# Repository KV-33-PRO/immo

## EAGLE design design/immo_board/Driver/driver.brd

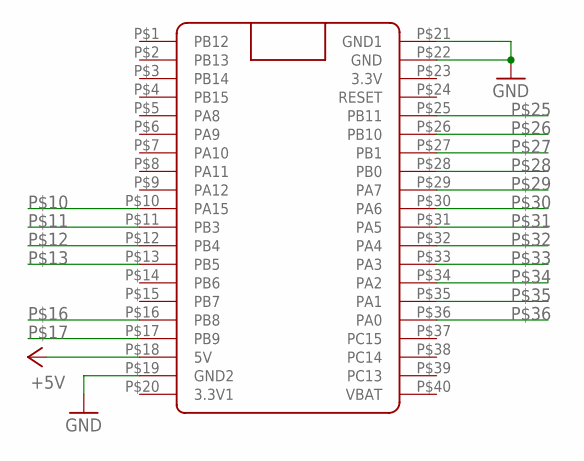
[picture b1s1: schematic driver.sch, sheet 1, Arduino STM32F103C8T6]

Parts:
U$1: STM32F103C8T6; BLUE_PILL_ADV

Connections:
+5V: U$1.P$18 (5V); also elsewhere on the board
GND: U$1.P$19 (GND2), U$1.P$21 (GND1), U$1.P$22 (GND); also elsewhere on the board
P$10: U$1.P$10 (PA15); also elsewhere on the board
P$11: U$1.P$11 (PB3); also elsewhere on the board
P$12: U$1.P$12 (PB4); also elsewhere on the board
P$13: U$1.P$13 (PB5); also elsewhere on the board
P$16: U$1.P$16 (PB8); also elsewhere on the board
P$17: U$1.P$17 (PB9); also elsewhere on the board
P$25: U$1.P$25 (PB11); also elsewhere on the board
P$26: U$1.P$26 (PB10); also elsewhere on the board
P$27: U$1.P$27 (PB1); also elsewhere on the board
P$28: U$1.P$28 (PB0); also elsewhere on the board
P$29: U$1.P$29 (PA7); also elsewhere on the board
P$30: U$1.P$30 (PA6); also elsewhere on the board
P$31: U$1.P$31 (PA5); also elsewhere on the board
P$32: U$1.P$32 (PA4); also elsewhere on the board
P$33: U$1.P$33 (PA3); also elsewhere on the board
P$34: U$1.P$34 (PA2); also elsewhere on the board
P$35: U$1.P$35 (PA1); also elsewhere on the board
P$36: U$1.P$36 (PA0); also elsewhere on the board

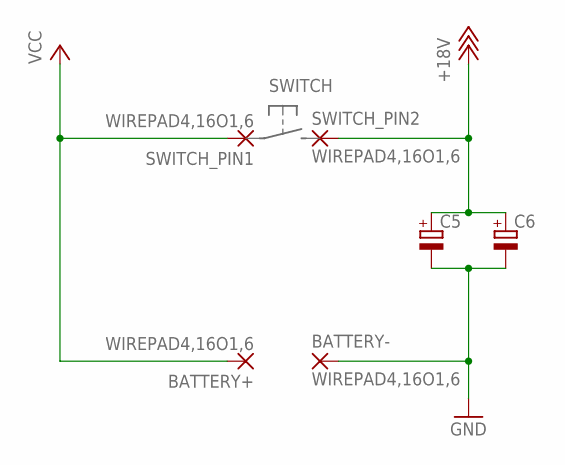
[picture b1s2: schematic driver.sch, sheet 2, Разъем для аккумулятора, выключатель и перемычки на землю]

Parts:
BATTERY+: WIREPAD4,16O1,6; 4,16O1,6
BATTERY-: WIREPAD4,16O1,6; 4,16O1,6
C5: CPOL-EUE5-8.5; E5-8,5
C6: CPOL-EUE2.5-5; E2,5-5
SWITCH_PIN1, SWITCH_PIN2: WIREPAD4,16O1,6; 4,16O1,6

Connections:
+18V: C5.+, C6.+, SWITCH_PIN2.1; also elsewhere on the board
GND: BATTERY-.1, C5.-, C6.-; also elsewhere on the board
VCC: BATTERY+.1, SWITCH_PIN1.1

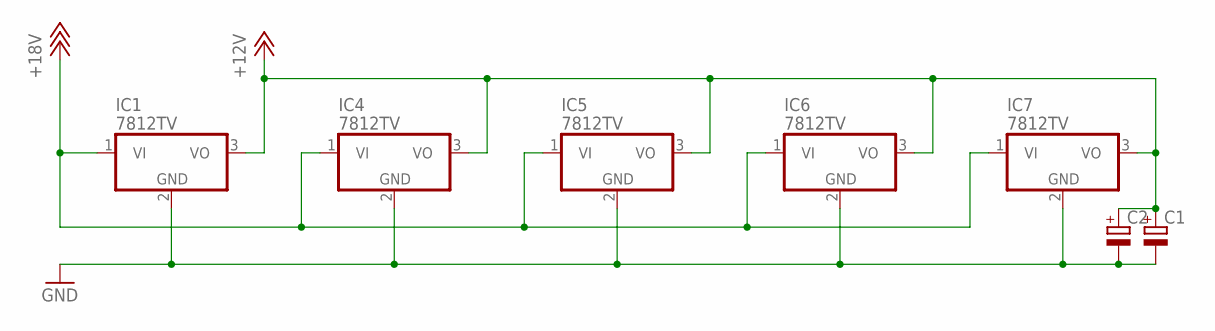
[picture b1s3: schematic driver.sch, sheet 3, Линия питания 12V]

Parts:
C1: CPOL-EUE5-8.5; E5-8,5
C2: CPOL-EUE2.5-5; E2,5-5
IC1, IC4, IC5, IC6, IC7: 7812TV; TO220V

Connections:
+12V: C1.+, C2.+, IC1.3 (VO), IC4.3 (VO), IC5.3 (VO), IC6.3 (VO), IC7.3 (VO); also elsewhere on the board
+18V: IC1.1 (VI), IC4.1 (VI), IC5.1 (VI), IC6.1 (VI), IC7.1 (VI); also elsewhere on the board
GND: C1.-, C2.-, IC1.2 (GND), IC4.2 (GND), IC5.2 (GND), IC6.2 (GND), IC7.2 (GND); also elsewhere on the board

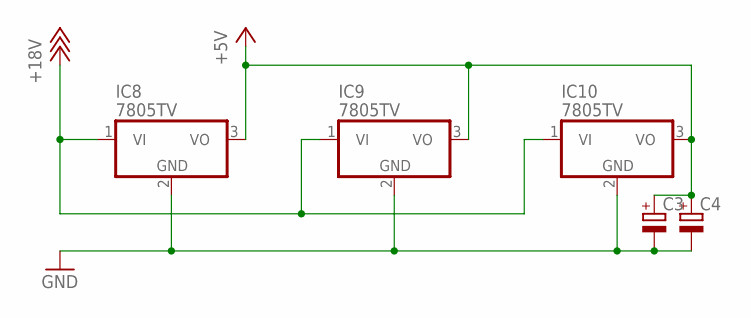
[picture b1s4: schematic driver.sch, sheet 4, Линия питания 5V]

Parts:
C3: CPOL-EUE2.5-5; E2,5-5
C4: CPOL-EUE5-8.5; E5-8,5
IC8, IC9, IC10: 7805TV; TO220V

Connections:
+5V: C3.+, C4.+, IC8.3 (VO), IC9.3 (VO), IC10.3 (VO); also elsewhere on the board
+18V: IC8.1 (VI), IC9.1 (VI), IC10.1 (VI); also elsewhere on the board
GND: C3.-, C4.-, IC8.2 (GND), IC9.2 (GND), IC10.2 (GND); also elsewhere on the board

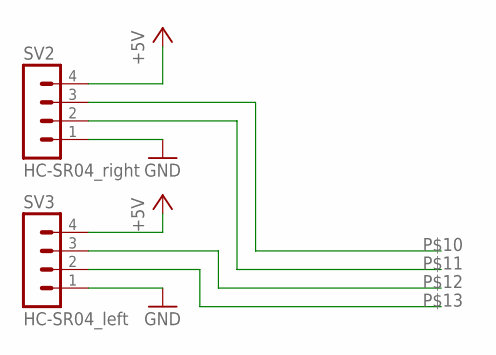
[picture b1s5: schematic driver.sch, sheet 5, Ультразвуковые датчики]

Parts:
SV2: HC-SR04_right; MA04-1
SV3: HC-SR04_left; MA04-1

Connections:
+5V: SV2.4, SV3.4; also elsewhere on the board
GND: SV2.1, SV3.1; also elsewhere on the board
P$10: SV2.3; also elsewhere on the board
P$11: SV2.2; also elsewhere on the board
P$12: SV3.3; also elsewhere on the board
P$13: SV3.2; also elsewhere on the board

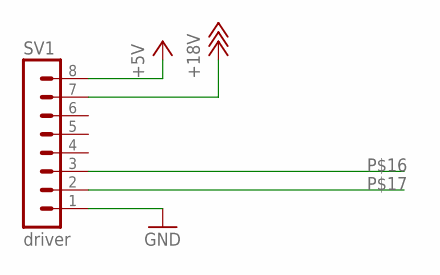
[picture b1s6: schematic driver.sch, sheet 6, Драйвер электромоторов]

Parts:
SV1: driver; MA08-1

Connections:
+5V: SV1.8; also elsewhere on the board
+18V: SV1.7; also elsewhere on the board
GND: SV1.1; also elsewhere on the board
P$16: SV1.3; also elsewhere on the board
P$17: SV1.2; also elsewhere on the board

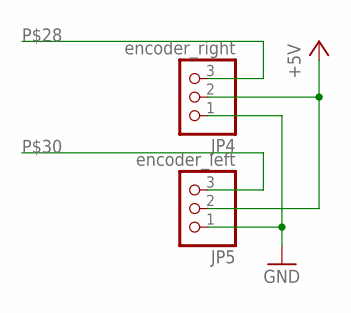
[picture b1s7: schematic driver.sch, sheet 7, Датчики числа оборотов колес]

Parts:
JP4: encoder_right; 1X03
JP5: encoder_left; 1X03

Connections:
+5V: JP4.2, JP5.2; also elsewhere on the board
GND: JP4.1, JP5.1; also elsewhere on the board
P$28: JP4.3; also elsewhere on the board
P$30: JP5.3; also elsewhere on the board

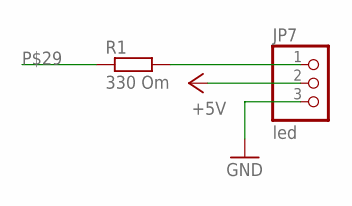
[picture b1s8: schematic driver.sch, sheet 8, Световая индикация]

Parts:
JP7: led; 1X03
R1: 330 Om; 0207/12

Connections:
+5V: JP7.2; also elsewhere on the board
GND: JP7.3; also elsewhere on the board
unnamed: JP7.1, R1.2
P$29: R1.1; also elsewhere on the board

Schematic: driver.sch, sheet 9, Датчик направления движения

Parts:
IC2: LM393N; DIL08
JP2: motor_direction; 1X02
R12, R13: 10 kOm; 0207/12

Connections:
+5V: IC2.8 (V+), R12.1, R13.2; also elsewhere on the board
GND: IC2.3 (+IN), IC2.4 (V-), IC2.5 (+IN); also elsewhere on the board
unnamed: IC2.2 (-IN), JP2.1
unnamed: IC2.6 (-IN), JP2.2
P$31: IC2.7 (OUT), R13.1; also elsewhere on the board
P$32: IC2.1 (OUT), R12.2; also elsewhere on the board

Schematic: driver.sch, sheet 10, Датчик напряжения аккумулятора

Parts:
JP6: battery_balance; 1_05X2MM
R2, R3, R4, R5: 3,3 kOm; 0207/15
R6, R7, R8, R9: 330 Om; 0207/15

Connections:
GND: JP6.5, R6.1, R7.1, R8.1, R9.1; also elsewhere on the board
unnamed: JP6.4, R5.2
unnamed: JP6.2, R4.2
unnamed: JP6.3, R3.2
unnamed: JP6.1, R2.2
P$33: R2.1, R6.2; also elsewhere on the board
P$34: R3.1, R7.2; also elsewhere on the board
P$35: R4.1, R8.2; also elsewhere on the board
P$36: R5.1, R9.2; also elsewhere on the board

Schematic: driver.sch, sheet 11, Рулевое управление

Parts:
IC3: 74LS241N; DIL20
JP1: dynamixel; 1X03

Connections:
+5V: IC3.20 (VCC); also elsewhere on the board
+12V: JP1.2; also elsewhere on the board
GND: IC3.10 (GND), JP1.1; also elsewhere on the board
unnamed: IC3.2 (A1), IC3.3 (Y4), JP1.3
P$25: IC3.18 (Y1); also elsewhere on the board
P$26: IC3.17 (A4); also elsewhere on the board
P$27: IC3.1 (G), IC3.19 (G); also elsewhere on the board

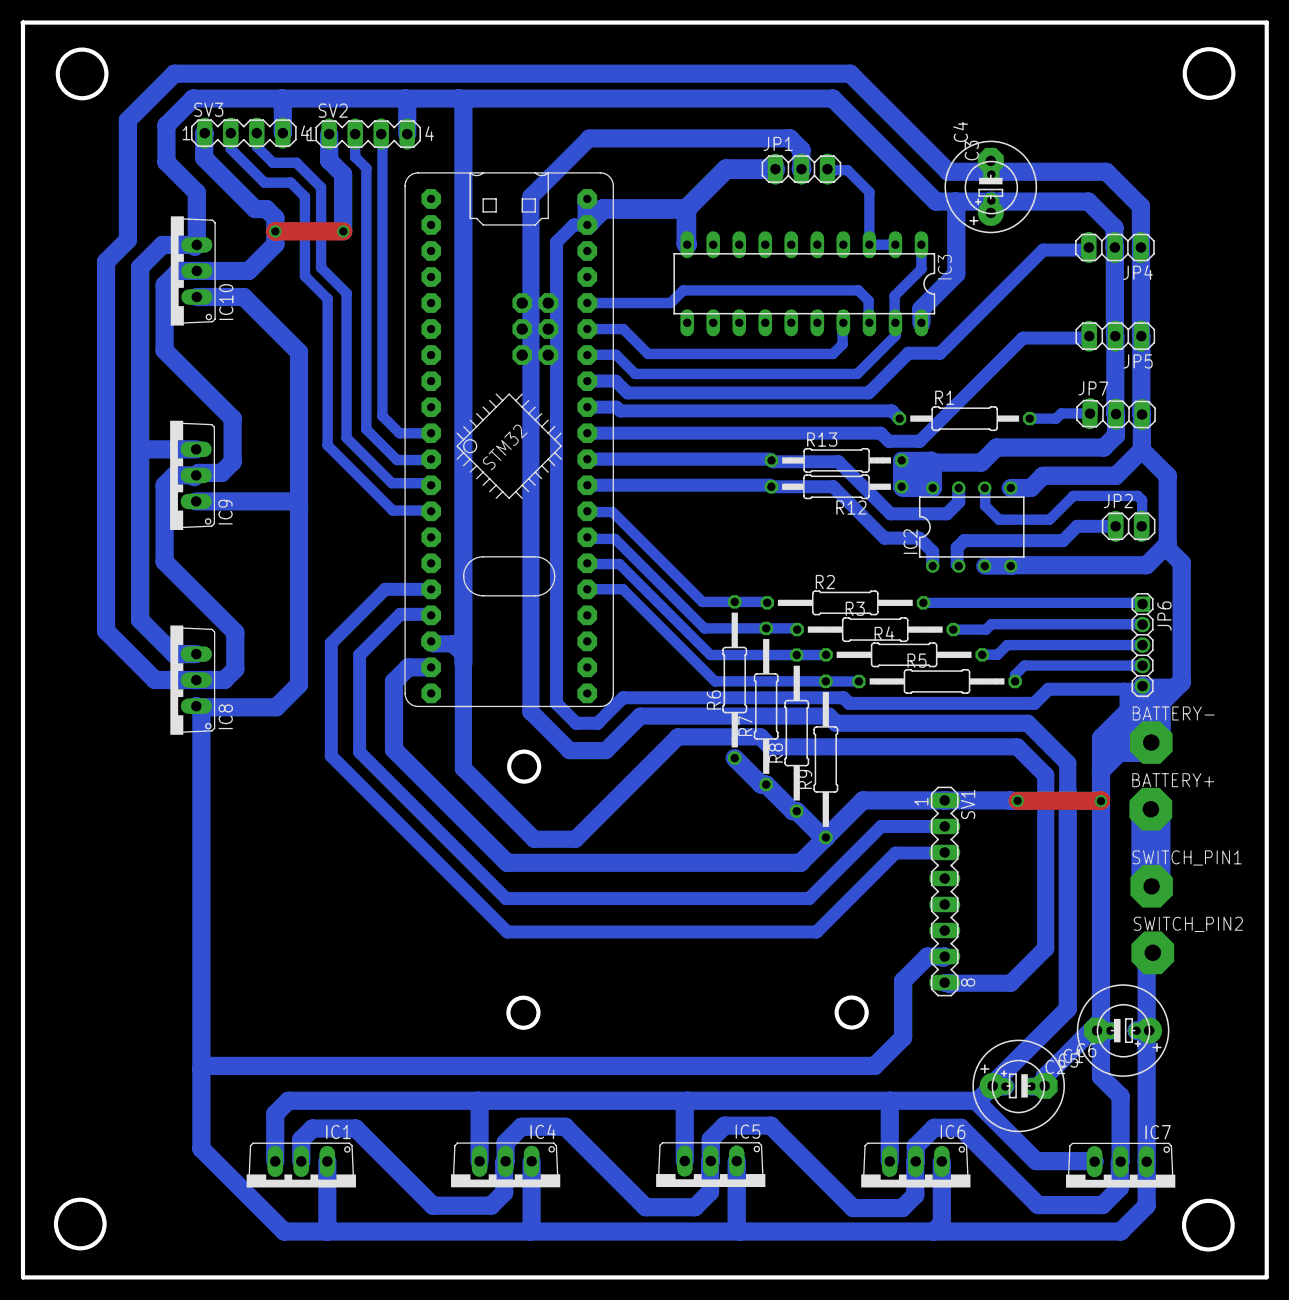
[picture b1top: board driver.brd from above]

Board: 2 copper layers, 121.4 x 122.5 mm, 41 parts (0 on the bottom side), 31 nets.

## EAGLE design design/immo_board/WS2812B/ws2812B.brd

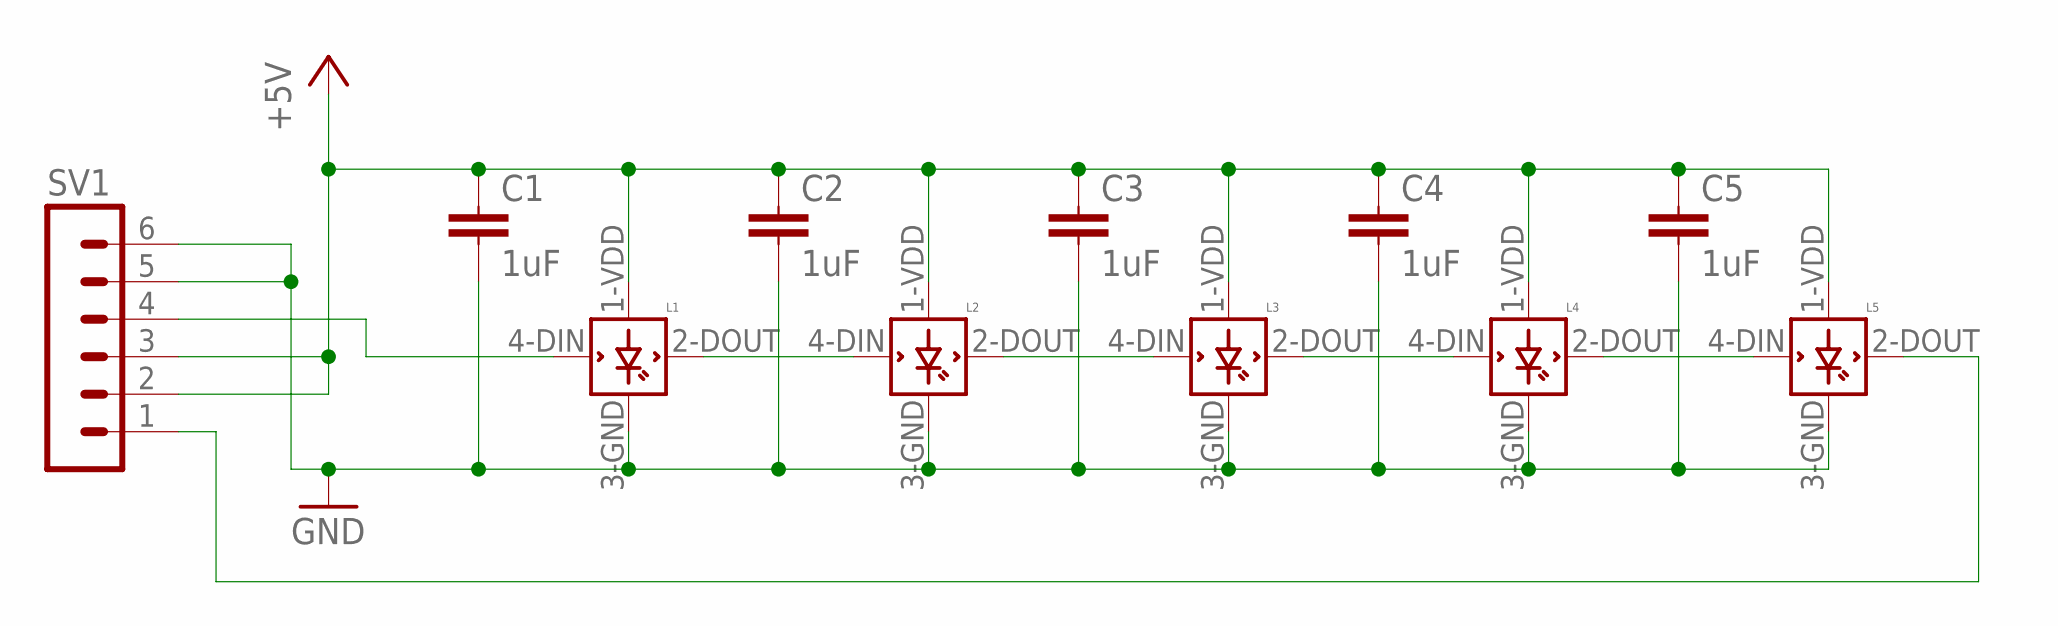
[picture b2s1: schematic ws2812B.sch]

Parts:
C1, C2, C3, C4, C5: 1uF; C10B4
L1, L2, L3, L4, L5: WS2812B
SV1: MA06-1

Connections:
+5V: C1.1, C2.1, C3.1, C4.1, C5.1, L1.1-VDD (VDD), L2.1-VDD (VDD), L3.1-VDD (VDD), L4.1-VDD (VDD), L5.1-VDD (VDD), SV1.2, SV1.3
GND: C1.2, C2.2, C3.2, C4.2, C5.2, L1.3-GND (GND), L2.3-GND (GND), L3.3-GND (GND), L4.3-GND (GND), L5.3-GND (GND), SV1.5, SV1.6
unnamed: L1.4-DIN (DIN), SV1.4
unnamed: L4.2-DOUT (DOUT), L5.4-DIN (DIN)
unnamed: L5.2-DOUT (DOUT), SV1.1
unnamed: L1.2-DOUT (DOUT), L2.4-DIN (DIN)
unnamed: L2.2-DOUT (DOUT), L3.4-DIN (DIN)
unnamed: L3.2-DOUT (DOUT), L4.4-DIN (DIN)

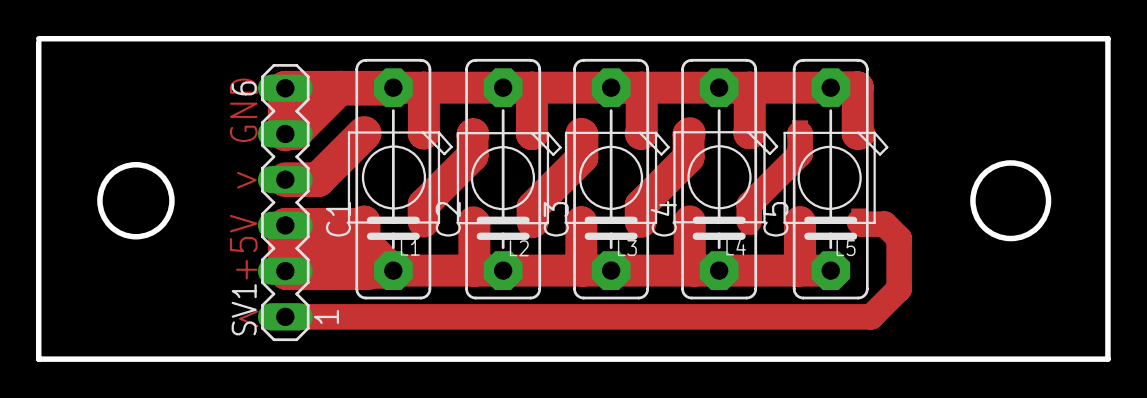
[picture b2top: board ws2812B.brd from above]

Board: 2 copper layers, 59.4 x 17.8 mm, 11 parts (0 on the bottom side), 8 nets.

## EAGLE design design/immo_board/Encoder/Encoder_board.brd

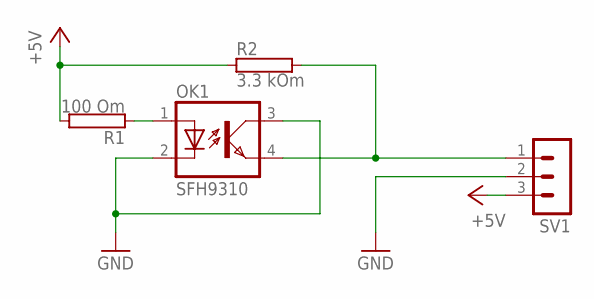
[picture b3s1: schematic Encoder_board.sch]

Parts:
OK1: SFH9310
R1: 100 Om; RS1/4
R2: 3.3 kOm; RS1/4
SV1: MA03-1

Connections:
+5V: R1.2, R2.1, SV1.3
GND: OK1.2 (C), OK1.3 (COL), SV1.2
unnamed: OK1.1 (A), R1.1
SIG: OK1.4 (EMIT), R2.2, SV1.1

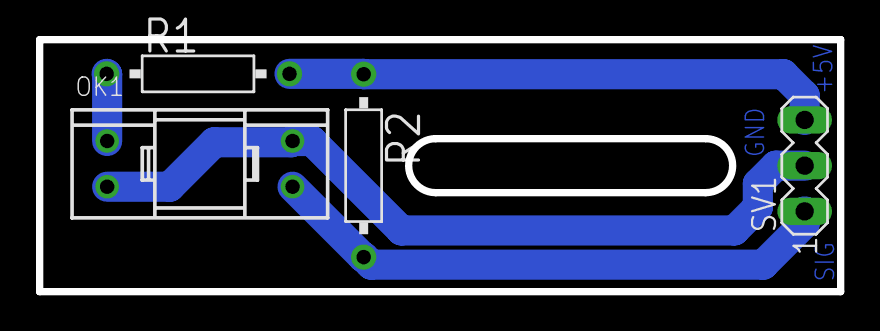
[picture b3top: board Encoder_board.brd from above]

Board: 2 copper layers, 44.5 x 14.0 mm, 4 parts (0 on the bottom side), 4 nets.

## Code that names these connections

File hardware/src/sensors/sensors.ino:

#include <ros.h>
#include <sensor_msgs/Range.h>
#include <Ultrasonic.h>
#include <SimpleKalmanFilter.h>

#define RATE_MS       20

ros::NodeHandle nh;

sensor_msgs::Range snr_l_msg;
sensor_msgs::Range snr_r_msg;

ros::Publisher snr_l_pub("range/front/left_snr", &snr_l_msg);
ros::Publisher snr_r_pub("range/front/right_snr", &snr_r_msg);

unsigned long last_ms;
Ultrasonic sonar_l(PA15, PB3);
Ultrasonic sonar_r(PB4, PB5);

SimpleKalmanFilter kf_l(2, 2, 0.01);
SimpleKalmanFilter kf_r(2, 2, 0.01);

void setup()
{
  nh.getHardware()->setBaud(500000);
  nh.initNode();
  nh.advertise(snr_l_pub);
  nh.advertise(snr_r_pub);

  snr_l_msg.header.frame_id =  "/left_snr";
  snr_l_msg.field_of_view = 0.10000000149;
  snr_l_msg.min_range = 0.3;
  snr_l_msg.max_range = 3.5;

  snr_r_msg.header.frame_id =  "/right_snr";
  snr_r_msg.field_of_view = 0.10000000149;
  snr_r_msg.min_range = 0.3;
  snr_r_msg.max_range = 3.5;
}

void loop()
{
  if ((millis() - last_ms) > RATE_MS) {
    last_ms = millis();

    snr_l_msg.range = kf_l.updateEstimate(sonar_l.read()/100.0);
    snr_l_msg.header.stamp = nh.now();
    snr_l_pub.publish(&snr_l_msg);

    snr_r_msg.range = kf_r.updateEstimate(sonar_r.read()/100.0);
    snr_r_msg.header.stamp = nh.now();
    snr_r_pub.publish(&snr_r_msg);

  }
  nh.spinOnce();
}

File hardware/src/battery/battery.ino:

#include <ros.h>
#include <sensor_msgs/BatteryState.h>

#define RATE_MS                   20       // задержка для публикации в топик

#define BAT_BALANCE_PIN_1         PA0      // вход для балансового порта батареи 1
#define BAT_BALANCE_PIN_2         PA1      // вход для балансового порта батареи 2
#define BAT_BALANCE_PIN_3         PA2      // вход для балансового порта батареи 3
#define BAT_BALANCE_PIN_4         PA3      // вход для балансового порта батареи 4

#define BAT_VOLTAGE_MAX           16.4             // максимальный вольтаж батареи (для расчета процентов)
#define BAT_VOLTAGE_MIN           14.0             // минимальный вольтаж батареи (для расчета процентов)
#define CELL_BAT                  4                // количество банок аккумулятора

float cell_voltage[CELL_BAT] = {0, 0, 0, 0};       //секции аккумулятора
unsigned long last_ms;

ros::NodeHandle nh;
sensor_msgs::BatteryState battery_msg;

ros::Publisher battery_pub("battery", &battery_msg);                    // инициализация издателя топика "battery"

void setup() {
  pinMode(BAT_BALANCE_PIN_1, INPUT_ANALOG);
  pinMode(BAT_BALANCE_PIN_2, INPUT_ANALOG);
  pinMode(BAT_BALANCE_PIN_3, INPUT_ANALOG);
  pinMode(BAT_BALANCE_PIN_4, INPUT_ANALOG);

  nh.getHardware()->setBaud(500000);
  nh.initNode();
  nh.advertise(battery_pub);

  battery_msg.header.frame_id =  "/battery";  //заголовок
  battery_msg.cell_voltage_length = CELL_BAT; //колличество банок (элементов массива)
  battery_msg.cell_voltage = cell_voltage;    //массив значений напряжений на банках аккумулятора
  battery_msg.present = true;                 //батарея присутствует
  battery_msg.power_supply_technology = 3;    //тип батареи LiPo
  battery_msg.power_supply_status = 2;        //разряжается
  battery_msg.power_supply_health = 0;        //неизвесно
}

void loop() {
  //Читаем и записываем значения напряжений в массив
  cell_voltage[0] = analog2voltage(BAT_BALANCE_PIN_1, 0);
  cell_voltage[1] = analog2voltage(BAT_BALANCE_PIN_2, 1);
  cell_voltage[2] = analog2voltage(BAT_BALANCE_PIN_3, 2);
  cell_voltage[3] = analog2voltage(BAT_BALANCE_PIN_4, 3);

  if (millis() - last_ms >= RATE_MS) {     //публикуем не чаще чем RATE_MS
    last_ms = millis();   //фиксируем последнее время публикации сообщения в топик

    // вычисляем напряжение 2-4 секций аккумулятора
    for(int i=CELL_BAT-1;i>0;i--)
    {
       cell_voltage[i] -= cell_voltage[i-1];
    }

    battery_msg.voltage = cell_voltage[0] + cell_voltage[1] + cell_voltage[2] + cell_voltage[3];            // расчет общего напряжения аккумулятора
    battery_msg.percentage = (battery_msg.voltage - BAT_VOLTAGE_MIN) / (BAT_VOLTAGE_MAX - BAT_VOLTAGE_MIN); // считаем количество процентов возможного ресурса батареи
    if (battery_msg.percentage < 0) {
      battery_msg.percentage = 0.0;
    }
    
    battery_msg.header.stamp = nh.now();     //фиксируем время сообщения
    battery_pub.publish(&battery_msg);       //публикуем сообщение в топик

    //обнуляем данные секций
    for(int i=0;i<CELL_BAT;i++)
    {
      cell_voltage[i] = 0.0;
    }
  }
  nh.spinOnce();
}

float analog2voltage(int bat_pin, int cell) {
  float analog = analogRead(bat_pin);                     //читаем значение и преобразем в вольты
  float count = 1.0;                                      //счетчик количества элементов для расчета среднего
  if (cell_voltage[cell] > 0.0)                           //если значение в массиве уже есть, то значит нужно выводить среднее (элементов 2)
  {
    count = 2.0;
  }
  
  if (analog > 10)                                        //устанавливаем порог напряжения (фильтр шумов на входе) 
  {
    float cell_volt = 0.0088316807*analog+0.031247058;    //линейная функция тренда для расчета вольтажа
    return (cell_voltage[cell] + cell_volt)  / count;     //замеряем и записываем, затем получим среднее
  }
  else
  {
    return 0.0;
  }
}

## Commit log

2018-12-01 Fix driver.ino. Add futs_qt_odometry.
2018-12-02 Rename "futs_qt_odometry" to "odometry". Fix odometry algorithms.
2018-12-03 Add odometry.launch. Fix odometry.
2018-12-04 Fix odometry algorithms
2018-12-05 Update sensors MCU firmware
    Sensors configuration and measuring formula are updated
2018-12-06 Update sensors MCU firmware
2018-12-06 Sensors MCU firmware
    Ultrasonic rangefinder now works
2018-12-06 (Sensors MCU)fix baud
2018-12-07 Fix driver algorithm. Add support dynamixel. Add libraries for arduino.
2018-12-13 Add design project
2018-12-13 Fix include libraries. Add ros_lib for STM32 and DynamixelSerial3.
2018-12-14 Fix driver firmware (for STM32). Add picture pinout STM32F103C8T6.
2018-12-14 Fix driver firmware. Add comments for driver firmware. Add directory misc.
2018-12-15 Add immo_board for encoders. Rename IMMO to immo_design_project.
2018-12-17 Fix algorithm odometry (direction of travel). Fix port to driver.launch.
2018-12-19 Add module for battery. Move driver, sensors to "src"
2018-12-21 Fix battery (function trend line). Add results experiment.
2018-12-21 Add PID regulator for speed control motors.
2018-12-22 Add driver_move package for tests. Add battery_module in driver hardware.
2018-12-23 Fix alghoritm driver odometry and driver_move.
2018-12-24 Fix firmware sensors (stm32). Add library Ultrasonic. Delete library NewPing.
2018-12-25 Add library SimpleKalmanFilter. Fix sensors (add kalman filter for sonars).
2018-12-26 Add board and scheme for WS2812B. Move Encoder_board.brd to immo_board/ Encoder.
2018-12-26 Add library for WS2812B leds. Add firmware led indication.
2018-12-27 Fix led firmware.
2018-12-29 Add electric scheme for driver board.
2018-12-30 Add board for driver. Fix electric scheme.
2019-01-16 Fix board for driver. Fix electric scheme.
2019-01-16 Fix driver firmware (pins). Fix led firmware.
2019-01-17 Fix driver firmware.
2019-01-17 Fix driver_move. Add param in launch.
2019-01-17 Fix launch driver (add start odometry). Fix launch odometry (respawn).
2019-01-31 Fix board and electrical scheme for Encoder, Driver, WS2812B.
2019-01-31 Fix tf in odometry_node.cpp
2019-01-31 Fix board and electric scheme. Add capacitors.
2019-01-31 Fix driver scheme (supply switch)
2019-01-31 Add engineering_books (chapter: electronics and programming) in documentation.
2019-02-07 Add instruction install STM32 in Arduino IDE.
2019-02-07 Fix Battery module for ROS, add Battery lib in driver. Add method angular2dynamixel for odometry.
2019-02-09 Add led_control_node and led_control.launch. Fix Battery library (example). Add Sensor_sonar library for ROS.
2019-02-11 Fix Sensor_sonar. Remove sensors.ino. Fix led_control_node.cpp. Add Led and Led_control library in modules_for_ROS.
2019-02-12 Rename Led_control to LedControl. Fix code LedControl.
2019-02-12 Add teleop_keyboard for move control. Add launch: teleop.launch and GO.launch (for start all nodes). Fix driver.launch.
2019-02-12 Update code in LedControl. Fix GO.launch. Remove launch sensors.
2019-02-13 Fix Led library.
2019-02-19 Fix LedControl library, teleop_key node. Add setup_config.
2019-02-20 Fix engine control in the absence of communication.
2019-02-21 Add setup_autostart ROS. Add immo.launch for autostart nodes. Fix Led library. Delete GO.launch.
2019-02-22 Rename library Led to LedWS2812BforSTM32. Fix in LedWS2812BforSTM32. Fix in LedControl.
2019-02-23 Fix LEDS library.
2019-02-23 Fix led indication. Add viu viu tr tr. Delete led.ino.
2019-02-25 Optimization LedWS2812BforSTM32. Fix launch files. Fix rviz config.
2019-02-26 Fix viu viu tr tr algorithm. Fix turn signal algorithm.
2019-03-02 Add navigation. Fix driver. Fix led_control. Fix hls_lfcd_lds.
2019-03-07 Fix lidar model platform. Fix map_server. Add info for setup.
2019-03-07 Fix launch file navigation.launch, navigation_rviz.launch. Add instruction setup git in qtcreator.
2019-03-09 Fix launch, fix map for navigation, rollback odometry.
2019-03-09 Fix driver firmware (no freeze)
2019-03-09 Rollback odometry_node.cpp (23.12.18)
2019-03-09 Add info for setup. Add stack navigation for model ankkerman.
2019-03-09 Add navigation config for model akkerman. Add simulator for navigation Add launch for navigation. Fix config in hector_slam.
2019-03-11 Add setup instruction for wifi hotspot with DNS, DHCP.
2019-03-11 Fix launch files. Fix info setup. Add script for remap ROS_MASTER.
2019-03-12 Fix name topic laser_scan. Add new map. Fix navigation config.
2019-03-13 Fix teb_navigate, immo.launch, lidar frame.
2019-03-13 Fix odometry by Chef
2019-03-14 Fix odometry problems
2019-03-14 Ignore *.user files
2019-03-14 Fix nav config, maps (poligon), frame for lidar and slam. Fix setup info.
2019-03-15 Fix odometry_node.cpp. Fix maps and params for navigation.
2019-03-16 Making kostyl
2019-03-19 Add graph_route and immo_planner
2019-03-19 Fix error in immo_planner
2019-03-19 Fix odometry
2019-03-19 Fix immo_launch
2019-03-19 Fix documentations
2019-03-19 Fix documentations... find error in engineering_book
2019-03-19 Add map hotel turist.
2019-03-19 Launch AMCL on car
2019-03-19 Launch AMCL
2019-03-19 Add sign reciver and detected. Fix odometry CMakeLists for correct first build.
2019-03-19 Fix launch files.
2019-03-19 Fix lidar and led_control launch.
2019-03-20 Fix graph_route
2019-03-20 Add map_msk_poligon. Fix pose robot (slam).
2019-03-20 Move by wall and correct odometry
2019-03-20 Fix route
2019-03-20 Auto stash before merge of "master" and "origin/master"
2019-03-20 Add moving by markers
2019-03-21 Config route
2019-03-21 Route config
2019-03-21 Fix graph_profest2.yaml
2020-11-18 Исправлен косяк с расчетом одометрии
